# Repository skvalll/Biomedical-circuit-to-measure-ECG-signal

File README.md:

# Biomedical Circuit for Basic ECG Signal Measurement

## Overview

This project focuses on the design of a basic ECG (Electrocardiogram) measurement circuit for heart rate signal acquisition. The circuit was designed using **KiCad**, including both **schematic design** and **PCB layout**.

The project is intended for basic academic and educational purposes, providing a simple implementation for studying ECG signal acquisition and analog circuit design.

## Features

* Basic ECG signal acquisition circuit
* Heart rate signal measurement
* Schematic design using KiCad
* PCB layout design using KiCad
* Basic analog signal conditioning

## Tools

* **KiCad** – Schematic and PCB design
* **PCB Design** – Component placement and routing
* **ECG Signal Acquisition** – Basic heart rate measurement

## Project Structure

```text
Biomedical-ECG-Circuit/
├── README.md
├── hardware/
│   └── ECG_Circuit.kicad_sch
│   └── ECG_Circuit.kicad_pcb
│   └── ECG_Circuit.kicad_pro
└── Images/
    ├── schematic.png
    └── pcb_layout.png
```

## Design

The project consists of two main design stages:

### Schematic

The schematic was developed in KiCad to define the electrical connections and signal-processing stages of the ECG measurement circuit.

### PCB Layout

The PCB layout was designed in KiCad based on the schematic, including component placement and PCB routing.

## Purpose

This project was developed as a basic electronics and PCB design project to practice:

* ECG signal acquisition
* Analog circuit design
* Schematic design
* PCB layout
* KiCad workflow

## Disclaimer

This project is intended for **academic and educational purposes only**. It is not a medical device and should not be used for medical diagnosis or clinical applications.

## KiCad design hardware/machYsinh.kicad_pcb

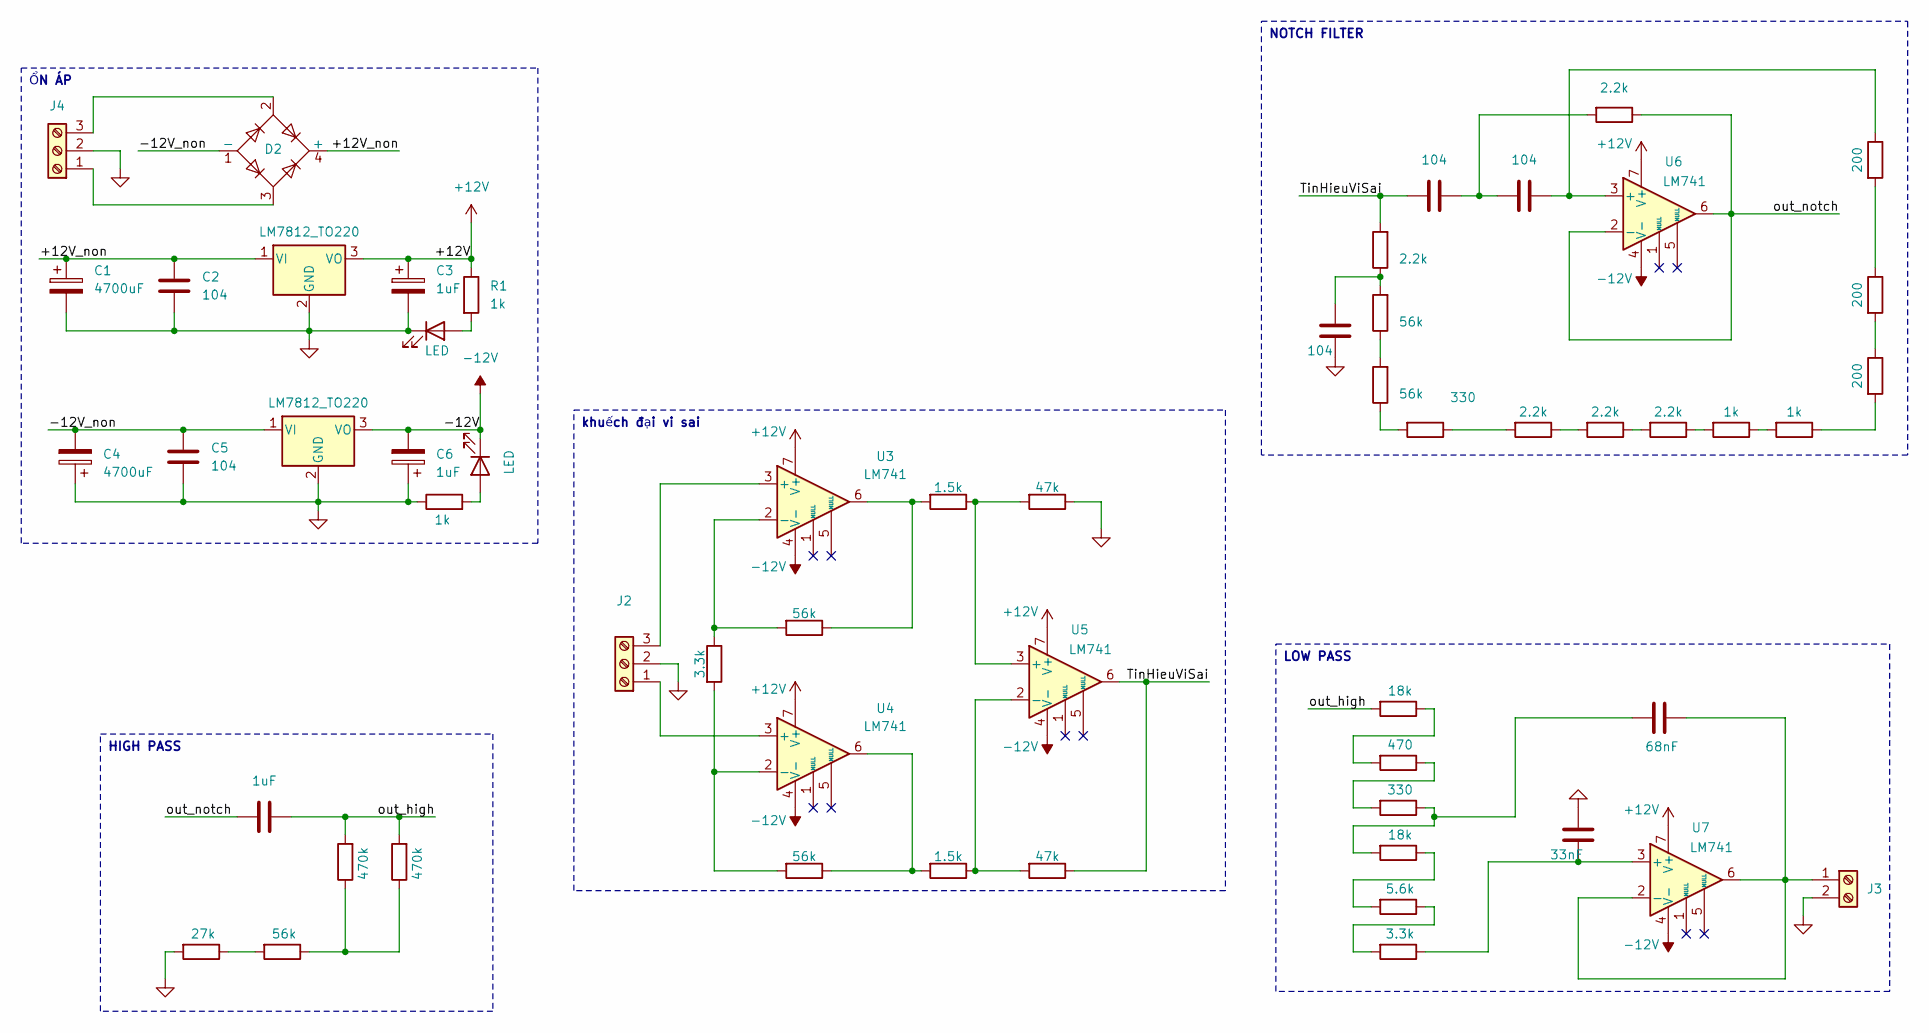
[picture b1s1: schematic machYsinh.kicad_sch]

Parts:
C1, C4: 4700uF; C_Radial_D16.0mm_H25.0mm_P7.50mm
C2, C5, C7, C8, C9: 104; C_Disc_D3.0mm_W1.6mm_P2.50mm
C3, C6: 1uF; CP_Radial_D5.0mm_P2.50mm
C10: 1uF; C_Disc_D4.3mm_W1.9mm_P5.00mm
C11: 33nF; C_Disc_D3.0mm_W1.6mm_P2.50mm
C12: 68nF; C_Disc_D3.0mm_W1.6mm_P2.50mm
D1, D3: LED; LED_D3.0mm_Clear
D2: B40C5000-3x00A; Diode_Bridge_32.0x5.6x17.0mm_P10.0mm_P7.5mm
J2, J4: Screw_Terminal_01x03; TerminalBlock_MaiXu_MX126-5.0-03P_1x03_P5.00mm
J3: Screw_Terminal_01x02; TerminalBlock_MaiXu_MX126-5.0-02P_1x02_P5.00mm
R1, R2, R17, R18: 1k; R_Axial_DIN0207_L6.3mm_D2.5mm_P10.16mm_Horizontal
R3, R4, R11, R12, R25: 56k; R_Axial_DIN0207_L6.3mm_D2.5mm_P10.16mm_Horizontal
R5, R32: 3.3k; R_Axial_DIN0207_L6.3mm_D2.5mm_P10.16mm_Horizontal
R6, R7: 1.5k; R_Axial_DIN0207_L6.3mm_D2.5mm_P10.16mm_Horizontal
R8, R9: 47k; R_Axial_DIN0207_L6.3mm_D2.5mm_P10.16mm_Horizontal
R10, R14, R15, R16, R22: 2.2k; R_Axial_DIN0207_L6.3mm_D2.5mm_P10.16mm_Horizontal
R13, R29: 330; R_Axial_DIN0207_L6.3mm_D2.5mm_P10.16mm_Horizontal
R19, R20, R21: 200; R_Axial_DIN0207_L6.3mm_D2.5mm_P10.16mm_Horizontal
R23, R24: 470k; R_Axial_DIN0207_L6.3mm_D2.5mm_P10.16mm_Horizontal
R26: 27k; R_Axial_DIN0207_L6.3mm_D2.5mm_P10.16mm_Horizontal
R27, R30: 18k; R_Axial_DIN0207_L6.3mm_D2.5mm_P10.16mm_Horizontal
R28: 470; R_Axial_DIN0207_L6.3mm_D2.5mm_P10.16mm_Horizontal
R31: 5.6k; R_Axial_DIN0207_L6.3mm_D2.5mm_P10.16mm_Horizontal
U1, U2: LM7812_TO220; TO-220-3_Vertical
U3, U4, U5, U6, U7: LM741; DIP-8_W7.62mm_LongPads

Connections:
+12V: C3.1, R1.1, U1.3 (VO), U3.7 (V+), U4.7 (V+), U5.7 (V+), U6.7 (V+), U7.7 (V+)
-12V: C6.2, D3.1 (K), U2.3 (VO), U3.4 (V-), U4.4 (V-), U5.4 (V-), U6.4 (V-), U7.4 (V-)
/+12V_non: C1.1, C2.1, D2.4 (+), U1.1 (VI)
/-12V_non: C4.2, C5.1, D2.1 (-), U2.1 (VI)
/TinHieuViSai: C8.1, R9.1, R10.2, U5.6
/out_high: C10.2, R23.2, R24.2, R27.2
/out_notch: C10.1, R22.1, U6.2 (-), U6.6
GND: C1.2, C2.2, C3.2, C4.1, C5.2, C6.1, C9.1, C11.2, D1.1 (K), J2.2, J3.2, J4.2, R2.1, R8.1, R26.2, U1.2 (GND), U2.2 (GND)
unnamed: C7.1, C8.2, R22.2
unnamed: C9.2, R10.1, R11.2
unnamed: C12.2, R29.1, R30.2
unnamed: D1.2 (A), R1.2
unnamed: D3.2 (A), R2.2
unnamed: J2.1, U4.3 (+)
unnamed: J2.3, U3.3 (+)
unnamed: C12.1, J3.1, U7.2 (-), U7.6
unnamed: D2.3, J4.1
unnamed: D2.2, J4.3
unnamed: R3.1, R6.2, U3.6
unnamed: R4.1, R7.2, U4.6
unnamed: R11.1, R12.2
unnamed: R12.1, R13.2
unnamed: R13.1, R14.2
unnamed: R14.1, R15.2
unnamed: R15.1, R16.2
unnamed: R16.1, R17.2
unnamed: R17.1, R18.2
unnamed: R18.1, R19.2
unnamed: R19.1, R20.2
unnamed: R20.1, R21.2
unnamed: R23.1, R24.1, R25.1
unnamed: R25.2, R26.1
unnamed: R27.1, R28.2
unnamed: R28.1, R29.2
unnamed: R30.1, R31.2
unnamed: R31.1, R32.2
unnamed: R3.2, R5.1, U3.2 (-)
unnamed: R4.2, R5.2, U4.2 (-)
unnamed: R6.1, R8.2, U5.3 (+)
unnamed: R7.1, R9.2, U5.2 (-)
unnamed: C7.2, R21.1, U6.3 (+)
unnamed: C11.1, R32.1, U7.3 (+)

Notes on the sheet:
HIGH PASS
LOW PASS
ỔN ÁP
NOTCH FILTER
khuếch đại vi sai

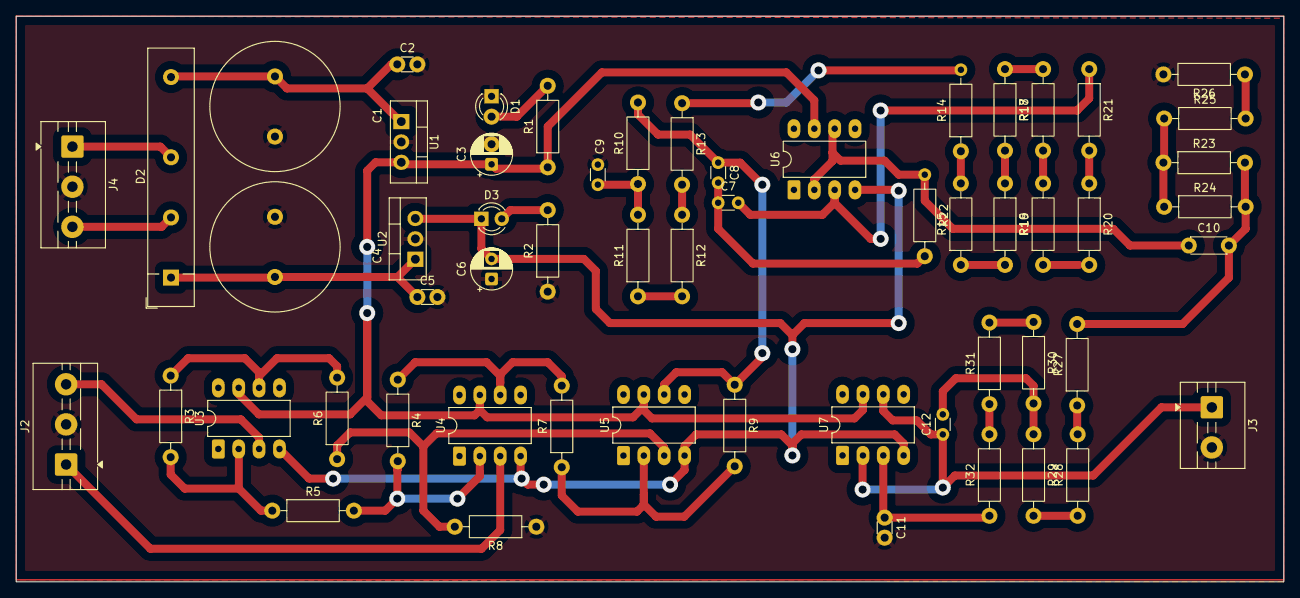
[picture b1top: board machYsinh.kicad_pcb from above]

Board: 2 copper layers, 158.0 x 70.5 mm, 57 parts (0 on the bottom side), 42 nets.
